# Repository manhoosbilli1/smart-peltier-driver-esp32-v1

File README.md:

# daanmem_esp32_board_FO2DABBFD842

Smart Peltier driver, ESP32-S3, v1 (v2 in active development)

## At a Glance

- **Status**: Partial / WIP
- **Board size**: 94.01 x 48.1 mm
- **Layers**: 2
- **Components**: 89
- **Key ICs**:
  - U1: AMS1117-3.3
  - U2: LM66200DRLR
  - U3: TPS62932
  - U4: ESP32-S3-WROOM-1-N16R8
  - U6: SM03B-SRSS-TB(LF)(SN)(P)
  - U7,U8: AHT20_C2757850
  - U9: TPS22811LRPWR_C17294173
  - U10: IRS44273LTRPBF

## Schematic

Full PDF: [reports/schematic.pdf](reports/schematic.pdf)

## Component Roles

- **ESP32-S3-WROOM-1** - main MCU; Wi-Fi/BT for remote temperature setpoint + telemetry
- **AMS1117-3.3** - 3.3 V LDO for the MCU core
- **LM66200DRLR** - dual-input ideal-diode / PowerPath controller for clean USB-vs-battery sourcing
- **AO3400A** - 30 V N-channel MOSFETs for switching the Peltier element / fan loads
- **H5VL06B** - small-signal transistors for gate driving / level shifting
- **MCP73831** - single-cell LiPo charger
- **USB-C (16-pin Type-C)** - power + data
- **JST-PH battery connector** (S2B-PH-SM4-TB) for LiPo cell

> v1 reached partial routing (90 footprints placed, 47 tracks, 26 zones). v2 is in active development.

## PCB

**Top copper**

**Bottom copper**

## Bill of Materials

| Refs | Value | Footprint | Qty | MPN | LCSC |
|------|-------|-----------|----:|-----|------|
| C1-C4,C8,C9 | 10uF | Capacitor_SMD:C_0805_2012Metric | 6 |  | [C6119887](https://www.lcsc.com/product-detail/_C6119887.html) |
| C5-C7,C13,C16,C19,C20 | 100nF | PCM_JLCPCB:C_0603 | 7 |  | [C14663](https://www.lcsc.com/product-detail/_C14663.html) |
| C11,C21 | 1uF | PCM_JLCPCB:C_0402 | 2 |  | [C52923](https://www.lcsc.com/product-detail/_C52923.html) |
| C12 | 33nF | PCM_JLCPCB:C_0603 | 1 |  | [C21117](https://www.lcsc.com/product-detail/_C21117.html) |
| C14 | 68pF | PCM_JLCPCB:R_0402 | 1 |  | [C76977](https://www.lcsc.com/product-detail/_C76977.html) |
| C15 | 10uF | PCM_JLCPCB:C_0402 | 1 |  | [C15525](https://www.lcsc.com/product-detail/_C15525.html) |
| C17 | 47uF | Capacitor_SMD:C_1210_3225Metric | 1 |  | [C77101](https://www.lcsc.com/product-detail/_C77101.html) |
| C18 | 100nF | PCM_JLCPCB:C_0805 | 1 |  | [C28233](https://www.lcsc.com/product-detail/_C28233.html) |
| C22 | 470uF | Capacitor_SMD:C_Elec_8x10.2 | 1 |  | [C141429](https://www.lcsc.com/product-detail/_C141429.html) |
| C23 | 3.3nF | PCM_JLCPCB:R_0603 | 1 |  | [C77036](https://www.lcsc.com/product-detail/_C77036.html) |
| C24 | 100nF | PCM_JLCPCB:C_0402 | 1 |  | [C1525](https://www.lcsc.com/product-detail/_C1525.html) |
| CN1-CN3 | S2B-PH-SM4-TB(LF)(SN) | :CONN-SMD_P2.00_S2B-PH-SM4-TB-LF-SN | 3 |  |  |
| D1,D5 | Red | PCM_JLCPCB:D_0805 | 2 |  | [C84256](https://www.lcsc.com/product-detail/_C84256.html) |
| D2-D4 | H5VL06B | PCM_JLCPCB:D_DFN0603-2L | 3 |  | [C7420373](https://www.lcsc.com/product-detail/_C7420373.html) |
| D6,D8 | 1N4007W | PCM_JLCPCB:D_SOD-123FL | 2 |  | [C18199088](https://www.lcsc.com/product-detail/_C18199088.html) |
| EN_TPS_JP1 | Jumper_2_Bridged | TestPoint:TestPoint_2Pads_Pitch2.54mm_Drill0.8mm | 1 |  |  |
| J1 | USB_C_Receptacle_USB2.0_16P | Connector_USB:USB_C_Receptacle_GCT_USB4110 | 1 |  |  |
| J2 | Peltier | TerminalBlock_Phoenix:TerminalBlock_Phoenix_MKDS-1,5-2-5.08_1x02_P5.08mm_Horizontal | 1 |  | [C7509570](https://www.lcsc.com/product-detail/_C7509570.html) |
| J3 | 12V_IN | TerminalBlock_Phoenix:TerminalBlock_Phoenix_MKDS-1,5-2-5.08_1x02_P5.08mm_Horizontal | 1 |  | [C7509570](https://www.lcsc.com/product-detail/_C7509570.html) |
| J4,J5 | Conn_01x02 | Connector_JST:JST_XH_B2B-XH-AM_1x02_P2.50mm_Vertical | 2 |  |  |
| JP1 | Jumper_2_Open | TestPoint:TestPoint_2Pads_Pitch2.54mm_Drill0.8mm | 1 |  |  |
| L1 | 470uH | Inductor_SMD:L_0402_1005Metric | 1 |  | [C5788770](https://www.lcsc.com/product-detail/_C5788770.html) |
| L2 | TMPC0624H-6R8MG-D | inductor_6.8u:IND-SMD_L7.0-W6.6 | 1 |  |  |
| Q1 | IRF8714 | :SOIC-8_L4.9-W3.9-P1.27-LS6.0-BL | 1 |  |  |
| Q2,Q3 | AO3400A | PCM_JLCPCB:Q_SOT-23 | 2 |  | [C20917](https://www.lcsc.com/product-detail/_C20917.html) |
| R1 | 2kΩ | PCM_JLCPCB:R_0402 | 1 |  | [C4109](https://www.lcsc.com/product-detail/_C4109.html) |
| R2,R3 | 5.1kΩ | PCM_JLCPCB:R_0402 | 2 |  | [C25905](https://www.lcsc.com/product-detail/_C25905.html) |
| R4 | 1kΩ | PCM_JLCPCB:R_0402 | 1 |  | [C11702](https://www.lcsc.com/product-detail/_C11702.html) |
| R5 | 100m | PCM_JLCPCB:R_0603 | 1 |  | [C713431](https://www.lcsc.com/product-detail/_C713431.html) |
| R6 | 510kΩ | PCM_JLCPCB:R_0402 | 1 |  | [C11616](https://www.lcsc.com/product-detail/_C11616.html) |
| R7 | 88.7k | PCM_JLCPCB:R_0402 | 1 |  | [C477808](https://www.lcsc.com/product-detail/_C477808.html) |
| R8,R12,R17,R22,R23,R25,R26,R29 | 10kΩ | PCM_JLCPCB:R_0402 | 8 |  | [C25744](https://www.lcsc.com/product-detail/_C25744.html) |
| R9 | 0Ω | PCM_JLCPCB:R_0402 | 1 |  | [C17168](https://www.lcsc.com/product-detail/_C17168.html) |
| R10 | 300Ω | PCM_JLCPCB:R_0402 | 1 |  | [C25102](https://www.lcsc.com/product-detail/_C25102.html) |
| R11 | 30.9k | Resistor_SMD:R_0402_1005Metric | 1 |  | [C2085168](https://www.lcsc.com/product-detail/_C2085168.html) |
| R13 | 6.8 | PCM_JLCPCB:R_0402 | 1 |  |  |
| R14,R15 | 4.7kΩ | PCM_JLCPCB:R_0402 | 2 |  | [C25900](https://www.lcsc.com/product-detail/_C25900.html) |
| R16,R24 | 100Ω | PCM_JLCPCB:R_0402 | 2 |  | [C25076](https://www.lcsc.com/product-detail/_C25076.html) |
| R18,R21,R27 | 47kΩ | PCM_JLCPCB:R_0402 | 3 |  | [C25792](https://www.lcsc.com/product-detail/_C25792.html) |
| R19 | 11k | PCM_JLCPCB:R_0402 | 1 |  | [C705643](https://www.lcsc.com/product-detail/_C705643.html) |
| R28 | 5.6kΩ | PCM_JLCPCB:R_0402 | 1 |  | [C25908](https://www.lcsc.com/product-detail/_C25908.html) |
| R30 | 953 | PCM_JLCPCB:R_0402 | 1 |  | [C852958](https://www.lcsc.com/product-detail/_C852958.html) |
| R31 | 470kΩ | PCM_JLCPCB:R_0402 | 1 |  | [C25790](https://www.lcsc.com/product-detail/_C25790.html) |
| RT1 | RT_TP | TestPoint:TestPoint_Pad_D1.0mm | 1 |  |  |
| S1,S2 | Tactile Button, 160gf | PCM_JLCPCB:SW-SMD_4P-L5.1-W5.1-P3.70-LS6.5-TL-2 | 2 |  | [C318884](https://www.lcsc.com/product-detail/_C318884.html) |
| TP1 | VBUS | TestPoint:TestPoint_Pad_1.0x1.0mm | 1 |  |  |
| TP2 | ST_R | TestPoint:TestPoint_Pad_D1.0mm | 1 |  |  |
| TP3 | 12V_OUT_TP | TestPoint:TestPoint_Pad_D1.0mm | 1 |  |  |
| TPS_ST1 | TPS_BST_TP | TestPoint:TestPoint_Pad_D1.0mm | 1 |  |  |
| U1 | AMS1117-3.3 | Package_TO_SOT_SMD:SOT-223-3_TabPin2 | 1 |  | [C6186](https://www.lcsc.com/product-detail/_C6186.html) |
| U2 | LM66200DRLR | LM66200:SOT-583-8_L2.1-W1.2-P0.50-LS1.6-BL | 1 |  |  |
| U3 | TPS62932 | Package_TO_SOT_SMD:SOT-583-8 | 1 |  | [C3032935](https://www.lcsc.com/product-detail/_C3032935.html) |
| U4 | ESP32-S3-WROOM-1-N16R8 | RF_Module:ESP32-S3-WROOM-1 | 1 |  | [C2913202](https://www.lcsc.com/product-detail/_C2913202.html) |
| U6 | SM03B-SRSS-TB(LF)(SN)(P) | :CONN-SMD_SM03B-SRSS-TB-LF-SN-P | 1 |  |  |
| U7,U8 | AHT20_C2757850 | aht20:SENSOR-SMD_L3.0-W3.0-P1.00-BR | 2 |  |  |
| U9 | TPS22811LRPWR_C17294173 | tps22811:VQFN-10_L2.0-W2.0-P0.45-TL | 1 |  |  |
| U10 | IRS44273LTRPBF | :SOT-23-5_L3.0-W1.7-P0.95-LS2.8-BR | 1 |  |  |

_18 of 57 line items don't have an LCSC code in the schematic - search [LCSC](https://www.lcsc.com/) or [JLC parts search](https://jlcsearch.tscircuit.com/) by MPN or footprint when sourcing._

## Files

- `daanmem_esp32_board_FO2DABBFD842.kicad_pro` - KiCad project
- `daanmem_esp32_board_FO2DABBFD842.kicad_sch` - schematic source
- `daanmem_esp32_board_FO2DABBFD842.kicad_pcb` - PCB layout source
- `reports/schematic.pdf` - full schematic (printable)
- `reports/bom.csv` - bill of materials
- `reports/pcb-top.svg`, `reports/pcb-bottom.svg` - copper artwork
- `reports/board-stats.json` - KiCad-generated board statistics

---

_Renders and metadata auto-generated by `Backup-KiCadProject.ps1` using KiCad 10.0._

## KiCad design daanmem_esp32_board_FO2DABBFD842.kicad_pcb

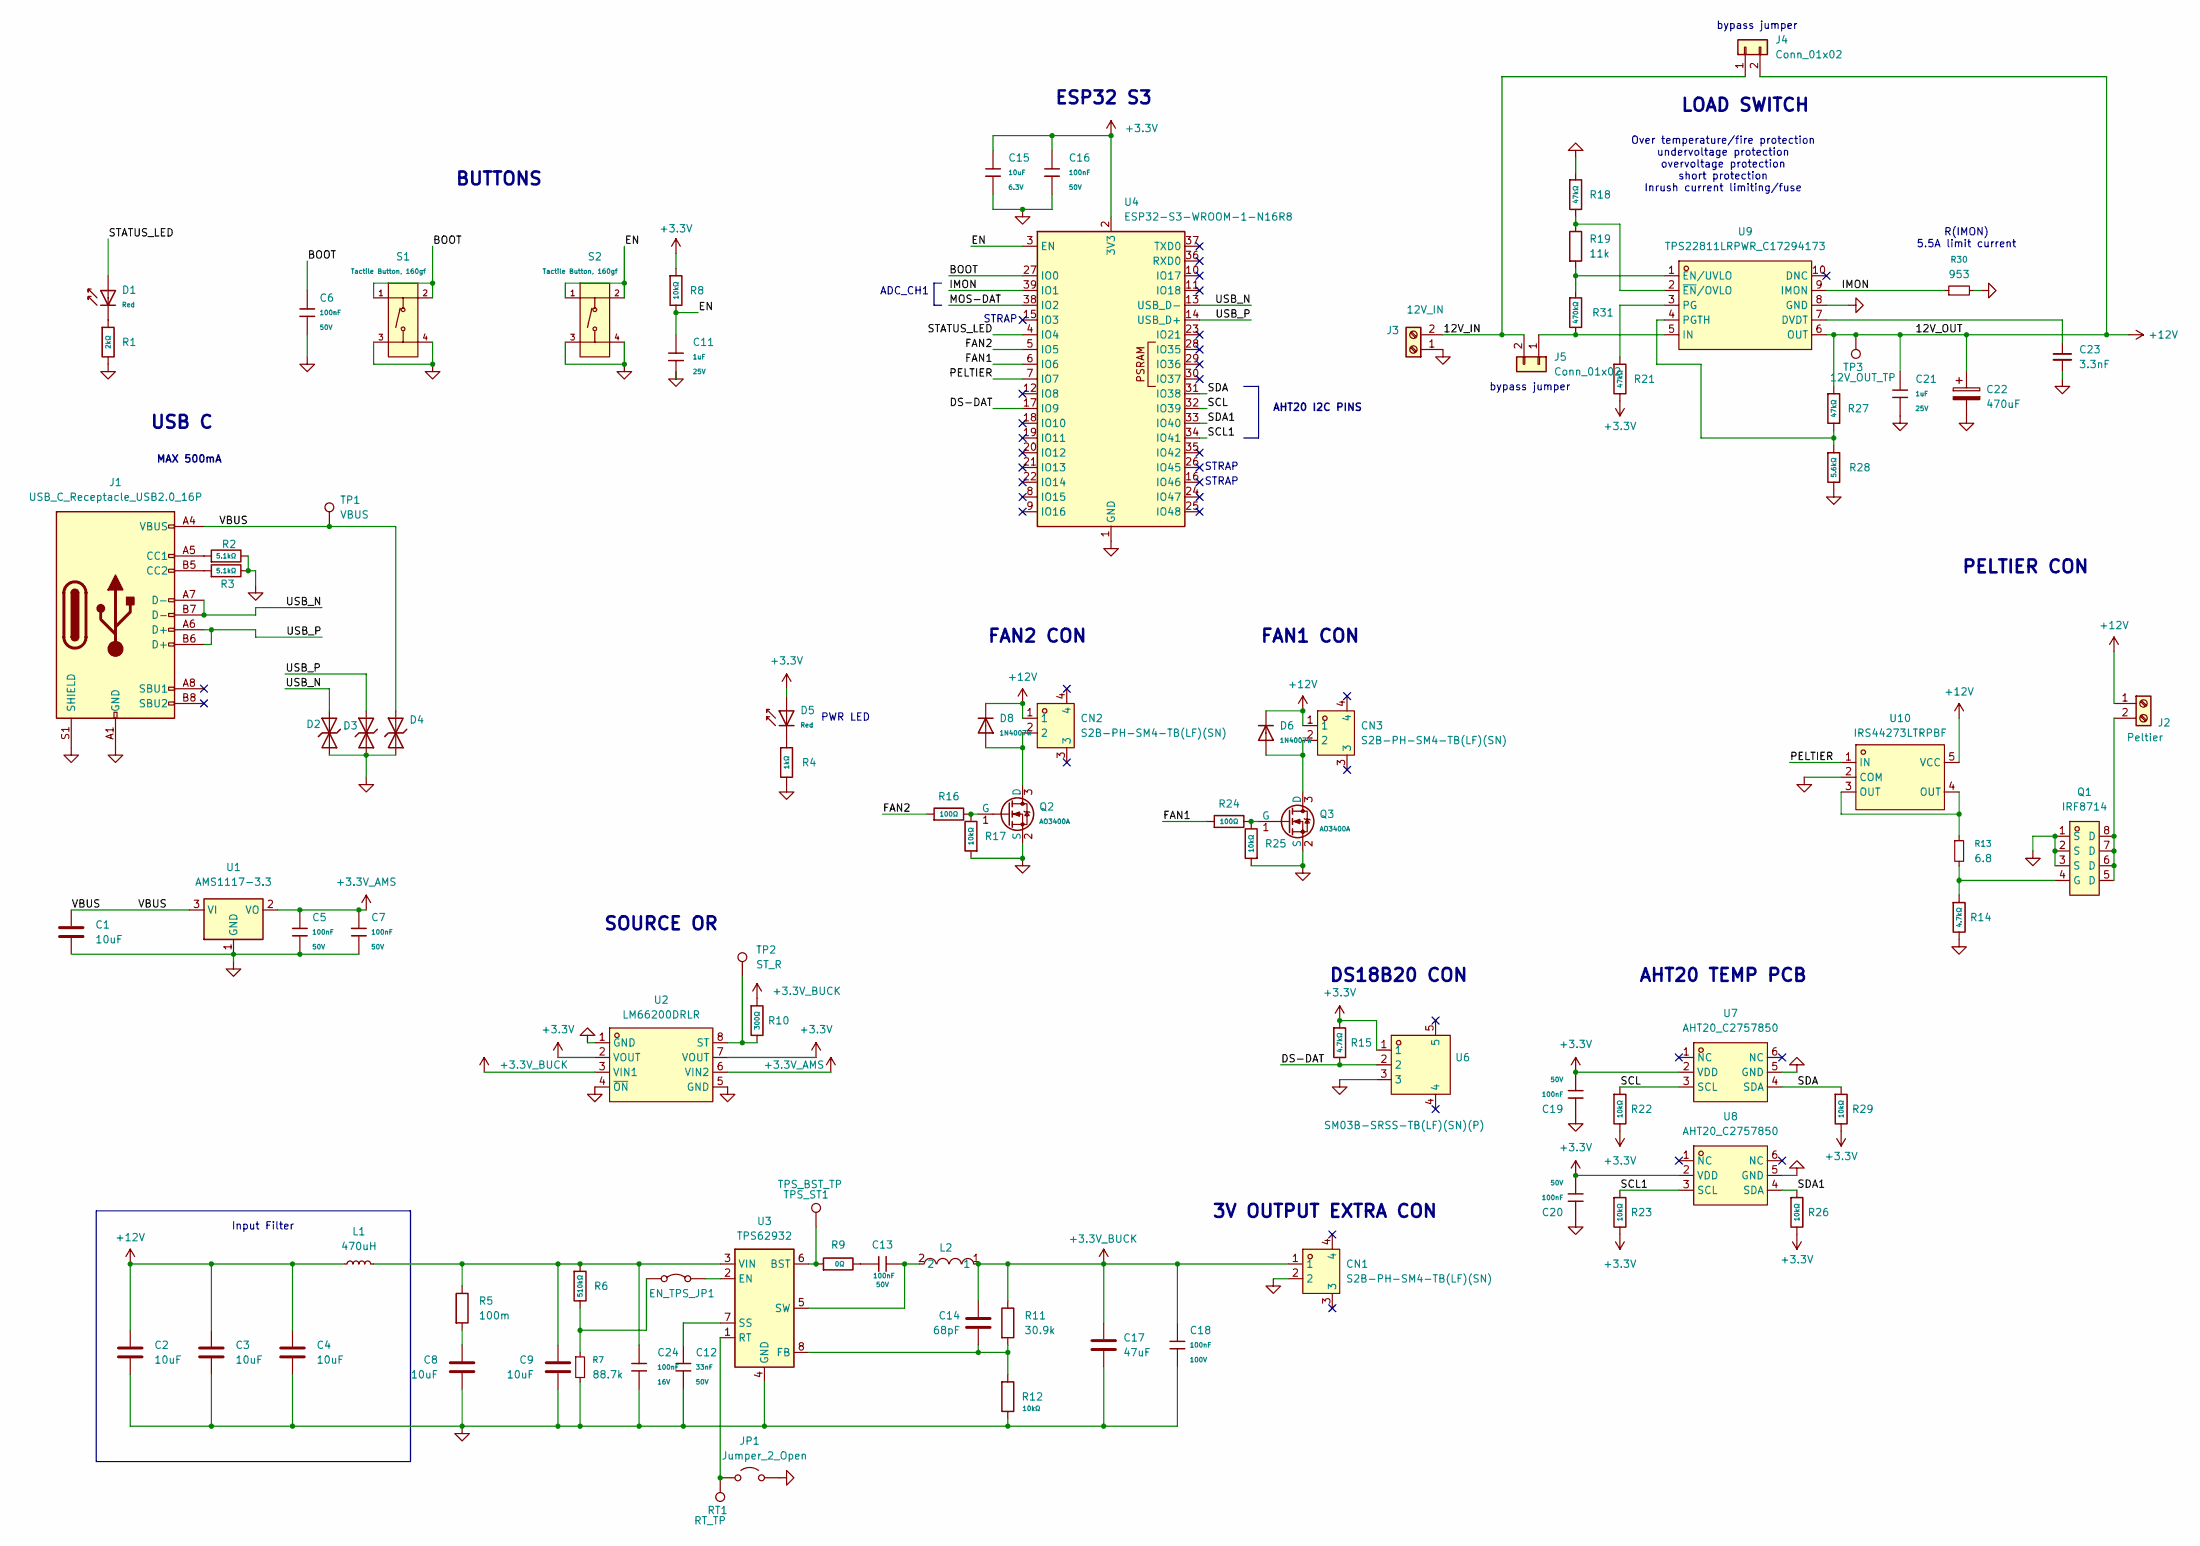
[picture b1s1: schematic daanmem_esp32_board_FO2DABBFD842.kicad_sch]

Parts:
C1, C2, C3, C4, C8, C9: 10uF; C_0805_2012Metric; LCSC C6119887
C5, C6, C7, C13, C16, C19, C20: 100nF; C_0603; Voltage Rated 50V; Tolerance ±10%; Part CC0603KRX7R9BB104; LCSC C14663
C11, C21: 1uF; C_0402; Voltage Rated 25V; Tolerance ±10%; Part CL05A105KA5NQNC; LCSC C52923
C12: 33nF; C_0603; Voltage Rated 50V; Tolerance ±10%; Part CL10B333KB8NNNC; LCSC C21117
C14: 68pF; R_0402; LCSC C76977
C15: 10uF; C_0402; Voltage Rated 6.3V; Tolerance ±20%; Part CL05A106MQ5NUNC; LCSC C15525
C17: 47uF; C_1210_3225Metric; LCSC C77101
C18: 100nF; C_0805; Voltage Rated 100V; Tolerance ±10%; Part CL21B104KCFNNNE; LCSC C28233
C22: 470uF; C_Elec_8x10.2; LCSC C141429
C23: 3.3nF; R_0603; LCSC C77036
C24: 100nF; C_0402; Voltage Rated 16V; Tolerance ±10%; Part CL05B104KO5NNNC; LCSC C1525
CN1, CN2, CN3: S2B-PH-SM4-TB(LF)(SN); CONN-SMD_P2.00_S2B-PH-SM4-TB-LF-SN; LCSC Part C295747
D1, D5: Red; D_0805; Forward Voltage (VF) 1.6V~2.6V; Part NCD0805R1; LCSC C84256
D2, D3, D4: H5VL06B; D_DFN0603-2L; Clamping Voltage@Ipp 10V; Breakdown Voltage (VBR) 5.6V; Part H5VL06B; LCSC C7420373
D6, D8: 1N4007W; D_SOD-123FL; Part 1N4007W; LCSC C18199088
EN_TPS_JP1: Jumper_2_Bridged; TestPoint_2Pads_Pitch2.54mm_Drill0.8mm
J1: USB_C_Receptacle_USB2.0_16P; USB_C_Receptacle_GCT_USB4110
J2: Peltier; TerminalBlock_Phoenix_MKDS-1,5-2-5.08_1x02_P5.08mm_Horizont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; LCSC C7509570
J3: 12V_IN; TerminalBlock_Phoenix_MKDS-1,5-2-5.08_1x02_P5.08mm_Horizont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; LCSC C7509570
J4, J5: Conn_01x02; JST_XH_B2B-XH-AM_1x02_P2.50mm_Vertical
JP1: Jumper_2_Open; TestPoint_2Pads_Pitch2.54mm_Drill0.8mm
L1: 470uH; L_0402_1005Metric; LCSC C5788770
L2: TMPC0624H-6R8MG-D; IND-SMD_L7.0-W6.6; LCSC Part C357230
Q1: IRF8714; SOIC-8_L4.9-W3.9-P1.27-LS6.0-BL; LCSC Part C5350863
Q2, Q3: AO3400A; Q_SOT-23; Part AO3400A; LCSC C20917
R1: 2kΩ; R_0402; Overload Voltage (Max) 50V; Tolerance ±1%; Part 0402WGF2001TCE; LCSC C4109
R2, R3: 5.1kΩ; R_0402; Overload Voltage (Max) 50V; Tolerance ±1%; Part 0402WGF5101TCE; LCSC C25905
R4: 1kΩ; R_0402; Overload Voltage (Max) 50V; Tolerance ±1%; Part 0402WGF1001TCE; LCSC C11702
R5: 100m; R_0603; LCSC C713431
R6: 510kΩ; R_0402; Overload Voltage (Max) 50V; Tolerance ±1%; Part 0402WGF5103TCE; LCSC C11616
R7: 88.7k; R_0402; LCSC C477808
R8, R12, R17, R22, R23, R25, R26, R29: 10kΩ; R_0402; Overload Voltage (Max) 50V; Tolerance ±1%; Part 0402WGF1002TCE; LCSC C25744
R9: 0Ω; R_0402; Overload Voltage (Max) 50V; Tolerance ±1%; Part 0402WGF0000TCE; LCSC C17168
R10: 300Ω; R_0402; Overload Voltage (Max) 50V; Tolerance ±1%; Part 0402WGF3000TCE; LCSC C25102
R11: 30.9k; R_0402_1005Metric; LCSC C2085168
R13: 6.8; R_0402
R14, R15: 4.7kΩ; R_0402; Overload Voltage (Max) 50V; Tolerance ±1%; Part 0402WGF4701TCE; LCSC C25900
R16, R24: 100Ω; R_0402; Overload Voltage (Max) 50V; Tolerance ±1%; Part 0402WGF1000TCE; LCSC C25076
R18, R21, R27: 47kΩ; R_0402; Overload Voltage (Max) 50V; Tolerance ±1%; Part 0402WGF4702TCE; LCSC C25792
R19: 11k; R_0402; LCSC C705643
R28: 5.6kΩ; R_0402; Overload Voltage (Max) 50V; Tolerance ±1%; Part 0402WGF5601TCE; LCSC C25908
R30: 953; R_0402; LCSC C852958
R31: 470kΩ; R_0402; Overload Voltage (Max) 50V; Tolerance ±1%; Part 0402WGF4703TCE; LCSC C25790
RT1: RT_TP; TestPoint_Pad_D1.0mm
S1, S2: Tactile Button, 160gf; SW-SMD_4P-L5.1-W5.1-P3.70-LS6.5-TL-2; Voltage Rating (Dc) 12V; Part TS-1187A-B-A-B; LCSC C318884
TP1: VBUS; TestPoint_Pad_1.0x1.0mm
TP2: ST_R; TestPoint_Pad_D1.0mm
TP3: 12V_OUT_TP; TestPoint_Pad_D1.0mm
TPS_ST1: TPS_BST_TP; TestPoint_Pad_D1.0mm
U1: AMS1117-3.3; SOT-223-3_TabPin2; LCSC C6186
U2: LM66200DRLR; SOT-583-8_L2.1-W1.2-P0.50-LS1.6-BL; LCSC Part C3235556
U3: TPS62932; SOT-583-8; LCSC C3032935
U4: ESP32-S3-WROOM-1-N16R8; ESP32-S3-WROOM-1; LCSC C2913202
U6: SM03B-SRSS-TB(LF)(SN)(P); CONN-SMD_SM03B-SRSS-TB-LF-SN-P; LCSC Part C160403
U7, U8: AHT20_C2757850; SENSOR-SMD_L3.0-W3.0-P1.00-BR; LCSC Part C2757850
U9: TPS22811LRPWR_C17294173; VQFN-10_L2.0-W2.0-P0.45-TL; LCSC Part C17294173
U10: IRS44273LTRPBF; SOT-23-5_L3.0-W1.7-P0.95-LS2.8-BR; LCSC Part C126909

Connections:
+3.3V_AMS: C5.1, C7.1, U1.2 (VO), U2.6 (VIN2)
+3.3V_BUCK: C14.1, C17.1, C18.1, CN1.1, L2.1, R10.1, R11.1, U2.3 (VIN1)
+12V: C2.1, C3.1, C4.1, C21.1, C22.1, CN2.1, CN3.1, D6.1, D8.1, J2.1, J4.2, L1.1, R27.1, TP3.1, U9.6 (OUT), U10.5 (VCC)
/12V_IN: J3.2, J4.1, J5.1, J5.2, R31.2, U9.5 (IN); also elsewhere on the board
/BOOT: C6.1, S1.1 (A), S1.2 (B), U4.27 (IO0)
/DS-DAT: R15.2, U4.17 (IO9), U6.2
/EN: C11.1, R8.2, S2.1 (A), S2.2 (B), U4.3 (EN)
/FAN1: R24.1, U4.6 (IO6)
/FAN2: R16.1, U4.5 (IO5)
/IMON: R30.1, U4.39 (IO1), U9.9 (IMON)
/MOS-DAT: U4.38 (IO2); also elsewhere on the board
/PELTIER: R13.1, U4.7 (IO7), U10.1 (IN), U10.3 (OUT), U10.4 (OUT)
/SCL: R22.1, U4.32 (IO39), U7.3 (SCL)
/SCL1: R23.1, U4.34 (IO41), U8.3 (SCL)
/SDA: R29.1, U4.31 (IO38), U7.4 (SDA)
/SDA1: R26.1, U4.33 (IO40), U8.4 (SDA)
/STATUS_LED: D1.2, U4.4 (IO4)
/USB_N: D2.2, J1.A7 (D-), J1.B7 (D-), U4.13 (USB_D-)
/USB_P: D3.2, J1.A6 (D+), J1.B6 (D+), U4.14 (USB_D+)
GND: C1.2, C2.2, C3.2, C4.2, C5.2, C6.2, C7.2, C8.2, C9.2, C11.2, C12.2, C15.2, C16.2, C17.2, C18.2, C19.1, C20.1, C21.2, C22.2, C23.2, C24.2, CN1.2, D2.1, D3.1, D4.1, J1.A1 (GND), J1.A12 (GND), J1.B1 (GND), J1.B12 (GND), J1.S1 (SHIELD), J3.1, JP1.2 (B), Q1.1 (S), Q1.2 (S), Q1.3 (S), Q2.2 (S), Q3.2 (S), R1.2, R2.2, R3.2, R4.2, R7.2, R12.2, R14.2, R17.1, R18.1, R25.1, R28.2, R30.2, S1.3 (C), S1.4 (D), S2.3 (C), S2.4 (D), U1.1 (GND), U2.1 (GND), U2.4 (~ON), U2.5 (GND), U3.4 (GND), U4.1 (GND), U4.40 (GND), U4.41 (GND), U6.3, U7.5 (GND), U8.5 (GND), U9.8 (GND), U10.2 (COM); also elsewhere on the board
unnamed: C8.1, R5.2
unnamed: C13.1, R9.2
unnamed: D1.1, R1.1
unnamed: D5.1, R4.1
unnamed: EN_TPS_JP1.1 (A), R6.2, R7.1
unnamed: EN_TPS_JP1.2 (B), U3.2 (EN)
unnamed: J1.A5 (CC1), R2.1
unnamed: J1.B5 (CC2), R3.1
unnamed 28: J2.2, Q1.5 (D), Q1.6 (D), Q1.7 (D), Q1.8 (D); also elsewhere on the board
unnamed: JP1.1 (A), RT1.1, U3.1 (RT)
unnamed: CN2.2, D8.2, Q2.3 (D)
unnamed: Q2.1 (G), R16.2, R17.2
unnamed: CN3.2, D6.2, Q3.3 (D)
unnamed: Q3.1 (G), R24.2, R25.2
unnamed 34: Q1.4 (G), R13.2, R14.1; also elsewhere on the board
unnamed: R10.2, TP2.1, U2.8 (ST)
unnamed: R9.1, TPS_ST1.1, U3.6 (BST)
unnamed: C14.2, R11.2, R12.1, U3.8 (FB)
unnamed: C12.1, U3.7 (SS)
unnamed: C13.2, L2.2, U3.5 (SW)
unnamed: C9.1, C24.1, L1.2, R5.1, R6.1, U3.3 (VIN)
unnamed: C23.1, U9.7 (DVDT)
unnamed 42: R19.2, R31.1, U9.1 (EN/UVLO); also elsewhere on the board
unnamed: R21.1, U9.3 (PG)
unnamed: R27.2, R28.1, U9.4 (PGTH)
unnamed: R18.2, R19.1, U9.2 (~EN/OVLO)

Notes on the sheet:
STRAP
LOAD SWITCH
Over temperature/fire protection undervoltage protection overvoltage protection short protection Inrush current limiting/fuse
MAX 500mA
ESP32 S3
bypass jumper
BUTTONS
ADC_CH1
Input Filter
SOURCE OR
FAN2 CON
FAN1 CON
3V OUTPUT EXTRA CON
R(IMON) 5.5A limit current
PELTIER CON
AHT20 I2C PINS
USB C
PWR LED
DS18B20 CON
AHT20 TEMP PCB

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
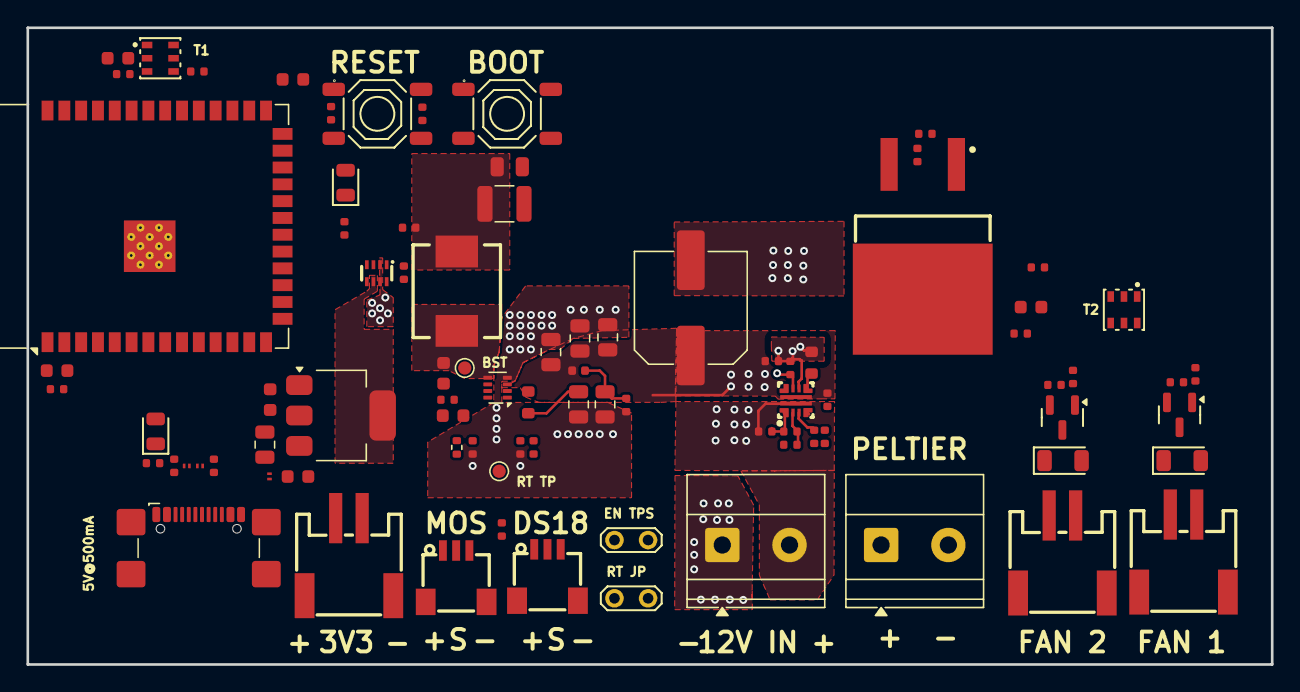
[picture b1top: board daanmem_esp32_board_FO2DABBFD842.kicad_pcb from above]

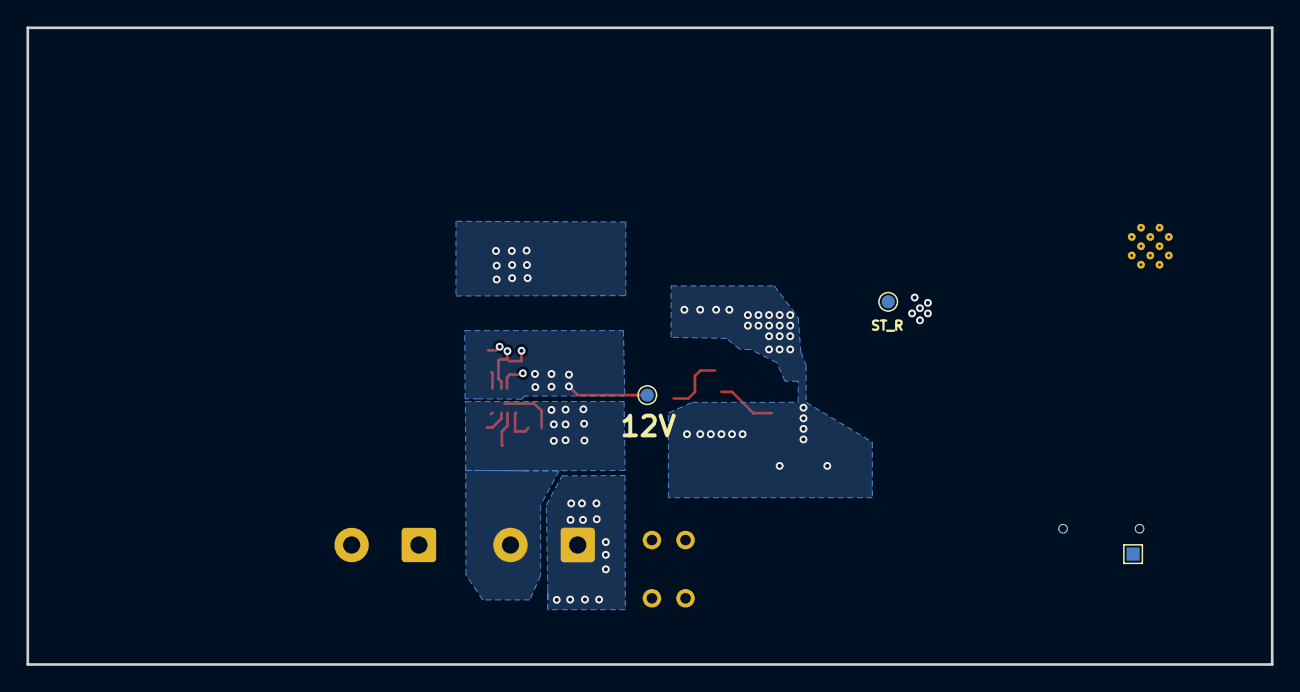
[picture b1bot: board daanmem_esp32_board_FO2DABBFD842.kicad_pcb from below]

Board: 2 copper layers, 94.0 x 48.1 mm, 89 parts (3 on the bottom side), 48 nets.

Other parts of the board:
Q4: IRF540NSTRLPBF; TO-263-2_L10.0-W9.1-P5.08-LS15.2-TL
R20: 47kΩ; R_0402
U5: SM03B-SRSS-TB(LF)(SN)(P); CONN-SMD_SM03B-SRSS-TB-LF-SN-P

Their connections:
/12V_IN: R20.2; also elsewhere on the board
/MOS-DAT: U5.2; also elsewhere on the board
GND: Q4.3 (S), U5.3; also elsewhere on the board
unnamed 28: Q4.4 (D); also elsewhere on the board
unnamed 34: Q4.1 (G); also elsewhere on the board
unnamed 42: R20.1; also elsewhere on the board

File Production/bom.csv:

Designator,Footprint,Quantity,Value,LCSC Part #
"C1, C2, C3, C4, C8, C9",0805,6,10uF,C6119887
"C11, C21",C_0402,2,1uF,C52923
C12,C_0603,1,33nF,C21117
"C13, C16, C19, C20, C5, C6, C7",C_0603,7,100nF,C14663
C14,R_0402,1,68pF,C76977
C15,C_0402,1,10uF,C15525
C17,1210,1,47uF,C77101
C18,C_0805,1,100nF,C28233
C22,C_Elec_8x10.2,1,470uF,C141429
C23,R_0603,1,3.3nF,C77036
C24,C_0402,1,100nF,C1525
"CN1, CN2, CN3",CONN-SMD_P2.00_S2B-PH-SM4-TB-LF-SN,3,S2B-PH-SM4-TB(LF)(SN),C295747
"D1, D5",D_0805,2,Red,C84256
"D2, D3, D4",D_DFN0603-2L,3,H5VL06B,C7420373
"D6, D8",D_SOD-123FL,2,1N4007W,C18199088
EN_TPS_JP1,TestPoint_2Pads_Pitch2.54mm_Drill0.8mm,1,Jumper_2_Bridged,
J1,USB_C_Receptacle_GCT_USB4110,1,USB_C_Receptacle_USB2.0_16P,
J2,"TerminalBlock_Phoenix_MKDS-1,5-2-5.08_1x02_P5.08mm_Horizontal",1,Peltier,C7509570
J3,"TerminalBlock_Phoenix_MKDS-1,5-2-5.08_1x02_P5.08mm_Horizontal",1,12V_IN,C7509570
JP1,TestPoint_2Pads_Pitch2.54mm_Drill0.8mm,1,Jumper_2_Open,
L1,0402,1,470uH,C5788770
L2,IND-SMD_L7.0-W6.6,1,TMPC0624H-6R8MG-D,C357230
"Q2, Q3",Q_SOT-23,2,AO3400A,C20917
Q4,TO-263-2_L10.0-W9.1-P5.08-LS15.2-TL,1,IRF540NSTRLPBF,C23982
"R1, R4",R_0402,2,2kΩ,C4109
R10,R_0402,1,300Ω,C25102
R11,0402,1,30.9k,C2085168
"R12, R17, R22, R23, R25, R26, R29, R8",R_0402,8,10kΩ,C25744
"R13, R16, R24",R_0402,3,100Ω,C25076
R14,R_0402,1,100kΩ,C25741
R15,R_0402,1,4.7kΩ,C25900
"R18, R20, R21, R27",R_0402,4,47kΩ,C25792
R19,R_0402,1,11k,C705643
"R2, R3",R_0402,2,5.1kΩ,C25905
R28,R_0402,1,5.6kΩ,C25908
R30,R_0402,1,953,C852958
R5,R_0603,1,100m,C713431
R6,R_0402,1,510kΩ,C11616
R7,R_0402,1,88.7k,C477808
R9,R_0402,1,0Ω,C17168
RT1,TestPoint_Pad_D1.0mm,1,RT_TP,
"S1, S2",SW-SMD_4P-L5.1-W5.1-P3.70-LS6.5-TL-2,2,"Tactile Button, 160gf",C318884
TP1,TestPoint_Pad_1.0x1.0mm,1,VBUS,
TP2,TestPoint_Pad_D1.0mm,1,ST_R,
TP3,TestPoint_Pad_D1.0mm,1,12V_OUT_TP,
TPS_ST1,TestPoint_Pad_D1.0mm,1,TPS_BST_TP,
U1,SOT-223-3_TabPin2,1,AMS1117-3.3,C6186
U2,SOT-583-8_L2.1-W1.2-P0.50-LS1.6-BL,1,LM66200DRLR,C3235556
U3,SOT-583-8,1,TPS62932,C3032935
U4,ESP32-S3-WROOM-1,1,ESP32-S3-WROOM-1-N16R8,C2913202
"U5, U6",CONN-SMD_SM03B-SRSS-TB-LF-SN-P,2,SM03B-SRSS-TB(LF)(SN)(P),C160403
"U7, U8",SENSOR-SMD_L3.0-W3.0-P1.00-BR,2,AHT20_C2757850,C2757850
U9,VQFN-10_L2.0-W2.0-P0.45-TL,1,TPS22811LRPWR_C17294173,C17294173

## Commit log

2026-05-18 Initial backup: schematic, PCB, renders, BOM
2026-05-18 Enrich README: schematic PNG, component roles, BOM table
